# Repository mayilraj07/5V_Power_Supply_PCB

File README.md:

# 5V Linear Power Supply Unit (PSU) PCB Design
A compact, robust, and professional-grade **5V Regulated DC Power Supply** designed using **KiCAD**. This project steps down and regulates an unregulated DC input into a stable 5V output suitable for powering microcontrollers (Arduino, ESP32, Raspberry Pi Pico), sensors, and low-power embedded devices.
---
## 📌 Features & Highlights
* **Stable 5V Output:** Constant voltage regulation using industry-standard voltage regulators.
* **Input Protection:** Filter capacitors to reduce voltage ripples and high-frequency noise.
* **Power Indicator:** On-board LED indicator for immediate visual status of the power supply.
* **Compact Footprint:** Optimized 2-layer PCB layout designed with professional component placement rules.
* **Noise Suppression:** Dedicated input/output decoupling capacitors placed adjacent to the regulator pins.
---
## 🛠️ Circuit Topology & Power Flow
The board follows a clean, single-direction power flow topology for minimal signal interference:
`DC Input / Connector` ➡️ `Input Filter Capacitors` ➡️ `5V Voltage Regulator` ➡️ `Output Filter Capacitors` ➡️ `Power LED Indicator` ➡️ `5V Terminal Output`
---
## 📐 Technical Specifications

| Specification | Value / Description |
| :--- | :--- |
| **Input Voltage** | 7V - 12V DC |
| **Output Voltage** | 5.0V DC (Regulated) |
| **EDA Tool Used** | KiCAD |
| **PCB Layers** | 2-Layer Board |
| **Power Track Width** | 0.8 mm – 1.0 mm (High Current Capacity) |
| **Signal Track Width** | 0.3 mm |
| **Copper Pour** | Top & Bottom Ground Plane (GND Zone) |

---
## 🖼️ Screenshots & Previews

### 3D Board View
### Top View

### Bottom View

### Isometric View

### PCB Layout Design

### Schematic Diagram

## 📂 Project Structure
```text
├── Hardware/           # KiCAD Schematic and PCB Layout files
├── Production/         # Production-ready Gerber files (.zip) and (BOM)
├── Docs/               # Images & 3D Render
└── README.md           # Project Overview
``` 
---

## 👤 Author & Acknowledgment
* **Designed by:** mayilraj07(https://github.com/mayilraj07)
* **Tool:** KiCAD EDA

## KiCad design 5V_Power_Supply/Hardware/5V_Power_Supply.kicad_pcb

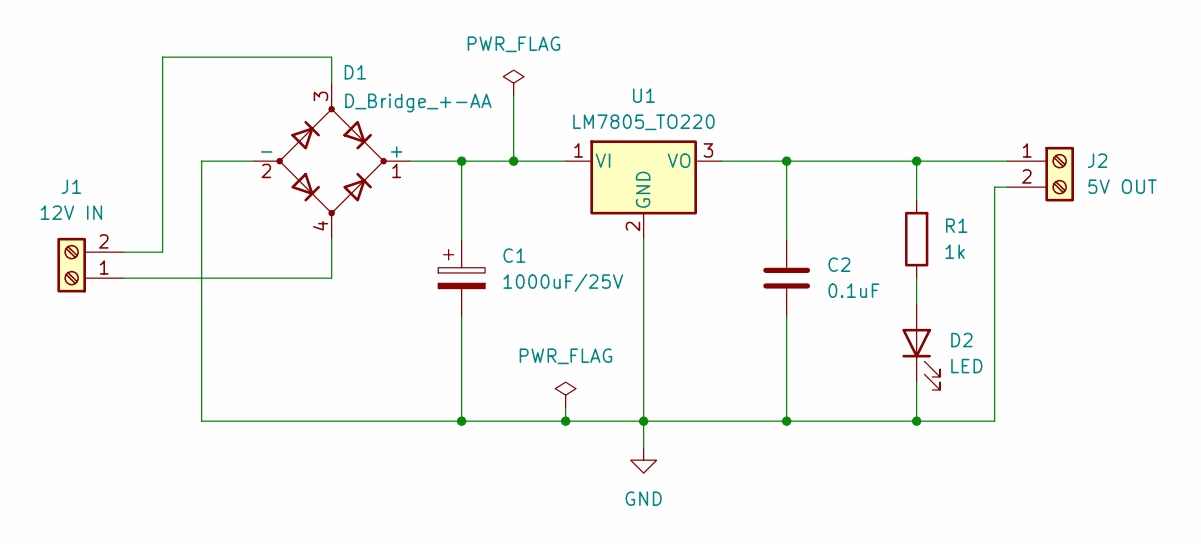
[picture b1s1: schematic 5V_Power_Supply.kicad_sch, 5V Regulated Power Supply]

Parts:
C1: 1000uF/25V; CP_Radial_D8.0mm_P3.50mm
C2: 0.1uF; C_Disc_D5.0mm_W2.5mm_P5.00mm
D1: D_Bridge_+-AA; Diode_Bridge_Round_D8.9mm
D2: LED; LED_D5.0mm
J1: 12V IN; TerminalBlock_Phoenix_MKDS-1,5-2_1x02_P5.00mm_Horizontal
J2: 5V OUT; TerminalBlock_Phoenix_MKDS-1,5-2_1x02_P5.00mm_Horizontal
R1: 1k; R_Axial_DIN0207_L6.3mm_D2.5mm_P7.62mm_Horizontal
U1: LM7805_TO220; TO-220-3_Vertical

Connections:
GND: C1.2, C2.2, D1.2 (-), D2.1 (K), J2.2, U1.2 (GND)
unnamed: C1.1, D1.1 (+), U1.1 (VI)
unnamed: D2.2 (A), R1.1
unnamed: D1.4, J1.1
unnamed: D1.3, J1.2
unnamed: C2.1, J2.1, R1.2, U1.3 (VO)

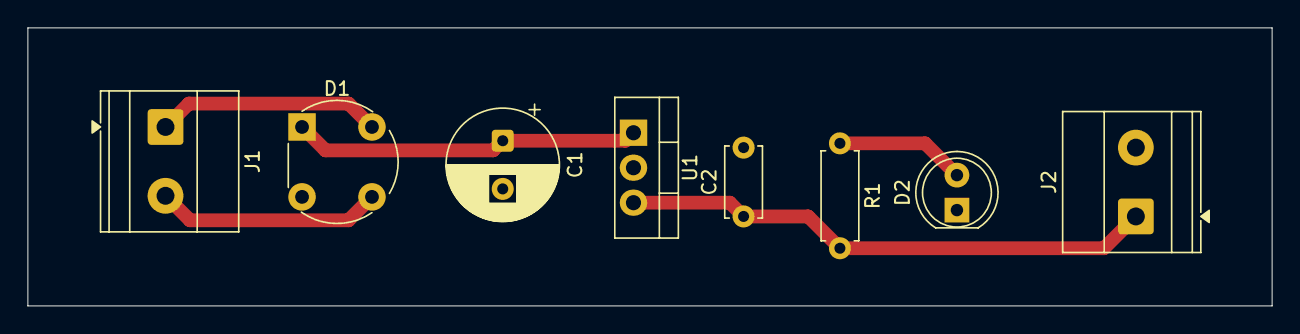
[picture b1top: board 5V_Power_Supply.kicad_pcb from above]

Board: 2 copper layers, 90.4 x 20.2 mm, 8 parts (0 on the bottom side), 6 nets.
